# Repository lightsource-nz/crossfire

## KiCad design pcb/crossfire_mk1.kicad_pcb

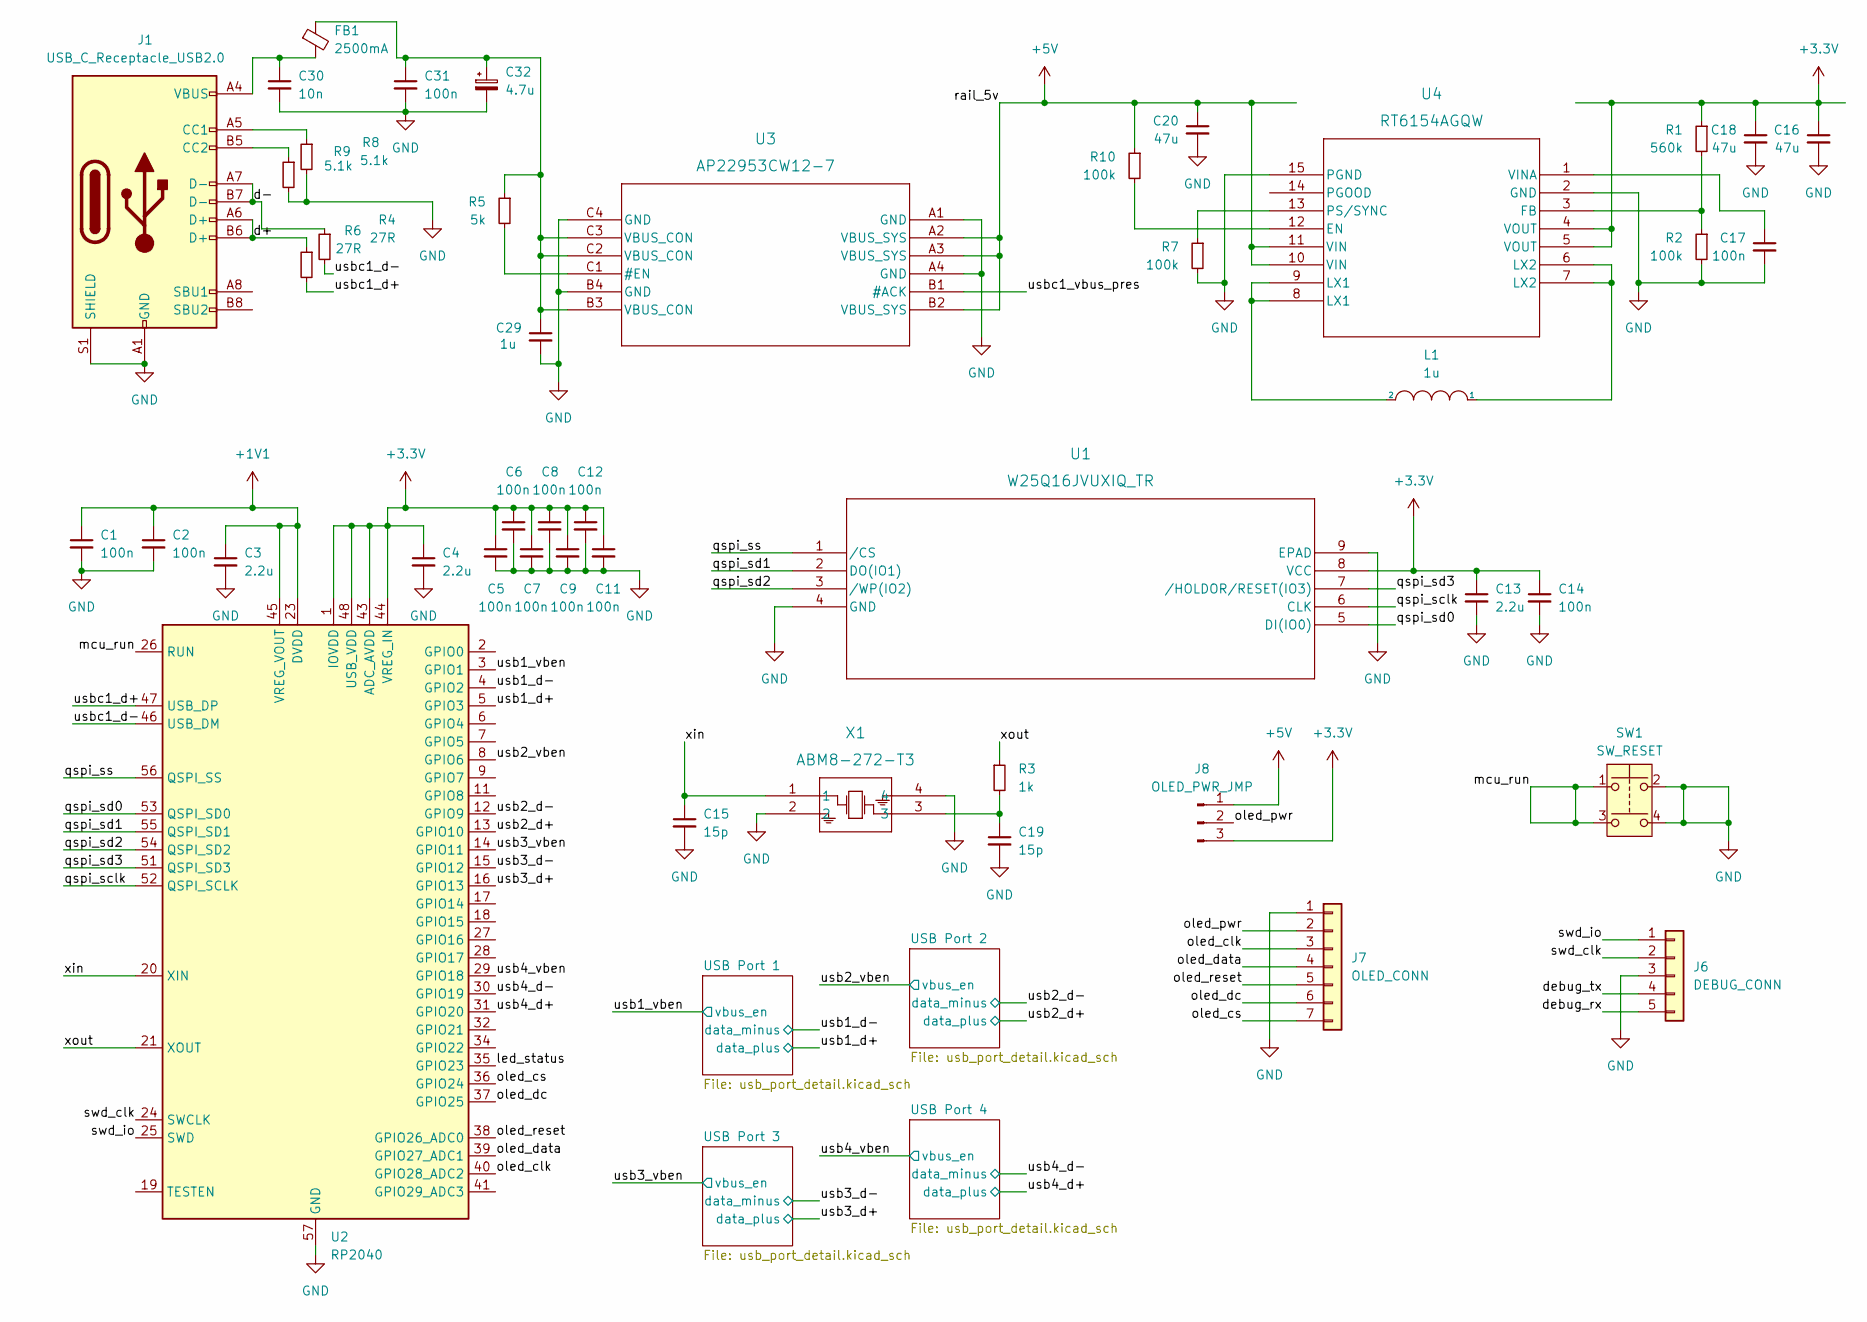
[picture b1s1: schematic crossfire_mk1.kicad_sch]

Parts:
C1, C2, C5, C6, C7, C8, C9, C11, C12, C14, C17, C31: 100n; C_0201_0603Metric
C3, C4: 2.2u; C_0402_1005Metric_Pad0.74x0.62mm_HandSolder
C13: 2.2u; C_0402_1005Metric
C15, C19: 15p; C_0201_0603Metric
C16, C18, C20: 47u; C_0805_2012Metric
C29: 1u; C_0201_0603Metric
C30: 10n; C_0201_0603Metric
C32: 4.7u; CP_Elec_4x5.4
FB1: 2500mA; L_0603_1608Metric
J1: USB_C_Receptacle_USB2.0; USB_C_Receptacle_GCT_USB4085
J6: DEBUG_CONN; PinHeader_1x05_P2.54mm_Vertical
J7: OLED_CONN; PinHeader_1x07_P2.54mm_Vertical
J8: OLED_PWR_JMP; PinHeader_1x03_P2.54mm_Vertical
L1: 1u; L_0805_2012Metric_Pad1.05x1.20mm_HandSolder
R1: 560k; R_0201_0603Metric
R2, R7, R10: 100k; R_0201_0603Metric
R3: 1k; R_0201_0603Metric
R4, R6: 27R; R_0201_0603Metric
R5: 5k; R_0201_0603Metric
R8, R9: 5.1k; R_0201_0603Metric
SW1: SW_RESET; Sumida_CPFC6D36NP-100M06
U1: W25Q16JVUXIQ_TR; W25Q16JVUXIQ_TR_PSON50P300X200X60-9N
U2: RP2040; QFN-56-1EP_7x7mm_P0.4mm_EP3.2x3.2mm
U3: AP22953CW12-7; BGA12_AP22953CW12-7_DIO
U4: RT6154AGQW; QFN_4AGQW_RIT
X1: ABM8-272-T3; ABM8-272-T3_ABR

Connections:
+1V1: C1.1, C2.1, C3.1, U2.23 (DVDD), U2.45 (VREG_VOUT), U2.50 (DVDD)
+3.3V: C4.1, C5.1, C6.1, C7.1, C8.1, C9.1, C11.1, C12.1, C13.1, C14.1, C16.1, C18.1, J8.3, R1.1, U1.8 (VCC), U2.1 (IOVDD), U2.10 (IOVDD), U2.22 (IOVDD), U2.33 (IOVDD), U2.42 (IOVDD), U2.43 (ADC_AVDD), U2.44 (VREG_IN), U2.48 (USB_VDD), U2.49 (IOVDD), U4.4 (VOUT), U4.5 (VOUT)
+5V: C20.1, J8.1, R10.1, U3.A2 (VBUS_SYS), U3.A3 (VBUS_SYS), U3.B2 (VBUS_SYS), U4.10 (VIN), U4.11 (VIN); also elsewhere on the board
/d+: J1.A6 (D+), J1.B6 (D+), R6.1
/d-: J1.A7 (D-), J1.B7 (D-), R4.1
/debug_rx: J6.5
/debug_tx: J6.4
/led_status: U2.35 (GPIO23)
/mcu_run: SW1.1, SW1.3, U2.26 (RUN)
/oled_clk: J7.3, U2.40 (GPIO28_ADC2)
/oled_cs: J7.7, U2.36 (GPIO24)
/oled_data: J7.4, U2.39 (GPIO27_ADC1)
/oled_dc: J7.6, U2.37 (GPIO25)
/oled_pwr: J7.2, J8.2
/oled_reset: J7.5, U2.38 (GPIO26_ADC0)
/qspi_sclk: U1.6 (CLK), U2.52 (QSPI_SCLK)
/qspi_sd0: U1.5 (DI(IO0)), U2.53 (QSPI_SD0)
/qspi_sd1: U1.2 (DO(IO1)), U2.55 (QSPI_SD1)
/qspi_sd2: U1.3 (/WP(IO2)), U2.54 (QSPI_SD2)
/qspi_sd3: U1.7 (/HOLDOR/RESET(IO3)), U2.51 (QSPI_SD3)
/qspi_ss: U1.1 (/CS), U2.56 (QSPI_SS)
/swd_clk: J6.2, U2.24 (SWCLK)
/swd_io: J6.1, U2.25 (SWD)
/usb1_d+: U2.5 (GPIO3); also elsewhere on the board
/usb1_d-: U2.4 (GPIO2); also elsewhere on the board
/usb1_vben: U2.3 (GPIO1); also elsewhere on the board
/usb2_d+: U2.13 (GPIO10); also elsewhere on the board
/usb2_d-: U2.12 (GPIO9); also elsewhere on the board
/usb2_vben: U2.8 (GPIO6); also elsewhere on the board
/usb3_d+: U2.16 (GPIO13); also elsewhere on the board
/usb3_d-: U2.15 (GPIO12); also elsewhere on the board
/usb3_vben: U2.14 (GPIO11); also elsewhere on the board
/usb4_d+: U2.31 (GPIO20); also elsewhere on the board
/usb4_d-: U2.30 (GPIO19); also elsewhere on the board
/usb4_vben: U2.29 (GPIO18); also elsewhere on the board
/usbc1_d+: R6.2, U2.47 (USB_DP)
/usbc1_d-: R4.2, U2.46 (USB_DM)
/usbc1_vbus_pres: U3.B1 (#ACK)
/xin: C15.1, U2.20 (XIN), X1.1
/xout: R3.1, U2.21 (XOUT)
GND: C1.2, C2.2, C3.2, C4.2, C5.2, C6.2, C7.2, C8.2, C9.2, C11.2, C12.2, C13.2, C14.2, C15.2, C16.2, C17.2, C18.2, C19.2, C20.2, C29.2, C30.2, C31.2, C32.2, J1.A1 (GND), J1.A12 (GND), J1.B1 (GND), J1.B12 (GND), J1.S1 (SHIELD), J6.3, J7.1, R2.2, R7.2, R8.2, R9.2, SW1.2, SW1.4, U1.4 (GND), U1.9 (EPAD), U2.57 (GND), U3.A1 (GND), U3.A4 (GND), U3.B4 (GND), U3.C4 (GND), U4.2 (GND), U4.15 (PGND), X1.2, X1.4; also elsewhere on the board
unnamed: C19.1, R3.2, X1.3
unnamed: C29.1, C31.1, C32.1, FB1.1, R5.1, U3.B3 (VBUS_CON), U3.C2 (VBUS_CON), U3.C3 (VBUS_CON)
unnamed: C30.1, FB1.2, J1.A4 (VBUS), J1.A9 (VBUS), J1.B4 (VBUS), J1.B9 (VBUS)
unnamed: J1.A5 (CC1), R8.1
unnamed: J1.B5 (CC2), R9.1
unnamed: L1.1, U4.6 (LX2), U4.7 (LX2)
unnamed: L1.2, U4.8 (LX1), U4.9 (LX1)
unnamed: R5.2, U3.C1 (#EN)
unnamed: R10.2, U4.12 (EN)
unnamed: R1.2, R2.1, U4.3 (FB)
unnamed: R7.1, U4.13 (PS/SYNC)
unnamed: C17.1, U4.1 (VINA)

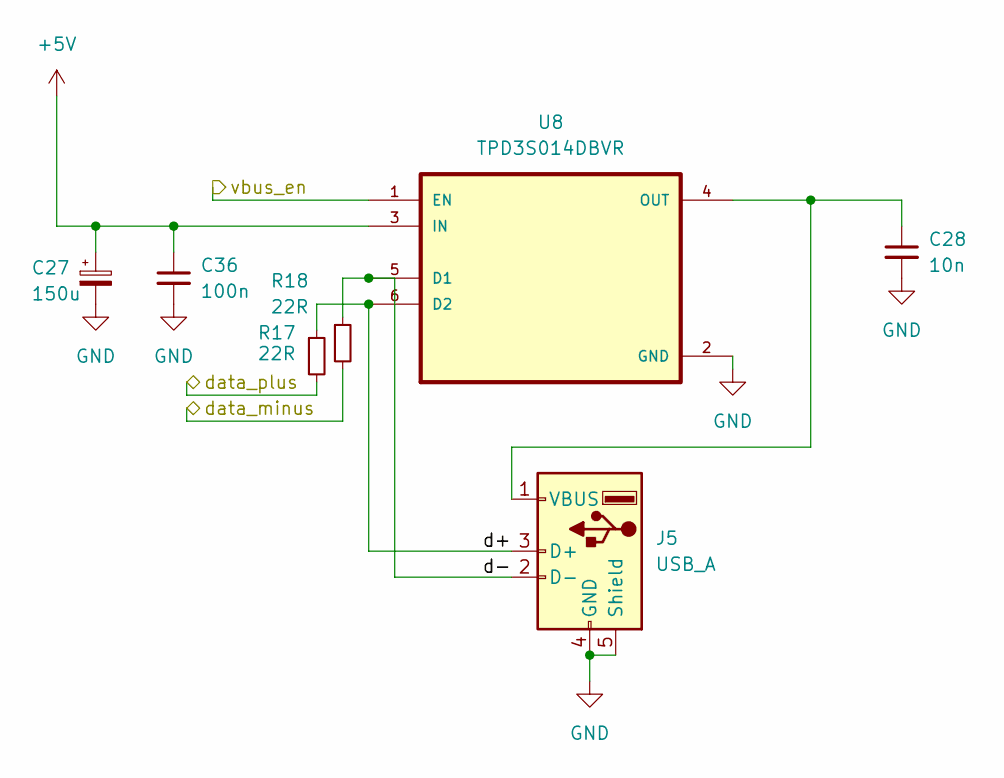
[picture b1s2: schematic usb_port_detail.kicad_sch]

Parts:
C27: 150u; CP_Elec_6.3x7.7
C28: 10n; C_0201_0603Metric
C36: 100n; C_0201_0603Metric
J5: USB_A; USB_A_Molex_67643_Horizontal
R17, R18: 22R; R_0201_0603Metric_Pad0.64x0.40mm_HandSolder
U8: TPD3S014DBVR; TPD3S014DBVR_SOT95P280X145-6N

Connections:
+5V: C27.1, C36.1, U8.3 (IN); also elsewhere on the board
/USB Port 4/d+: J5.3 (D+), R17.1, U8.6 (D2)
/USB Port 4/d-: J5.2 (D-), R18.1, U8.5 (D1)
/usb4_d+: R17.2; also elsewhere on the board
/usb4_d-: R18.2; also elsewhere on the board
/usb4_vben: U8.1 (EN); also elsewhere on the board
GND: C27.2, C28.2, C36.2, J5.4 (GND), J5.5 (Shield), U8.2 (GND); also elsewhere on the board
unnamed: C28.1, J5.1 (VBUS), U8.4 (OUT)

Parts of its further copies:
C21, C23, C25: 150u; CP_Elec_6.3x7.7
C22, C24, C26: 10n; C_0201_0603Metric
C33, C34, C35: 100n; C_0201_0603Metric
J2, J3, J4: USB_A; USB_A_Molex_67643_Horizontal
R11, R12, R13, R14, R15, R16: 22R; R_0201_0603Metric_Pad0.64x0.40mm_HandSolder
U5, U6, U7: TPD3S014DBVR; TPD3S014DBVR_SOT95P280X145-6N

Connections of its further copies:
+5V: C21.1, C23.1, C25.1, C33.1, C34.1, C35.1, U5.3 (IN), U6.3 (IN), U7.3 (IN); also elsewhere on the board
/USB Port 1/d+: J2.3 (D+), R11.1, U5.6 (D2)
/USB Port 1/d-: J2.2 (D-), R12.1, U5.5 (D1)
/USB Port 2/d+: J3.3 (D+), R13.1, U6.6 (D2)
/USB Port 2/d-: J3.2 (D-), R14.1, U6.5 (D1)
/USB Port 3/d+: J4.3 (D+), R15.1, U7.6 (D2)
/USB Port 3/d-: J4.2 (D-), R16.1, U7.5 (D1)
/usb1_d+: R11.2; also elsewhere on the board
/usb1_d-: R12.2; also elsewhere on the board
/usb1_vben: U5.1 (EN); also elsewhere on the board
/usb2_d+: R13.2; also elsewhere on the board
/usb2_d-: R14.2; also elsewhere on the board
/usb2_vben: U6.1 (EN); also elsewhere on the board
/usb3_d+: R15.2; also elsewhere on the board
/usb3_d-: R16.2; also elsewhere on the board
/usb3_vben: U7.1 (EN); also elsewhere on the board
GND: C21.2, C22.2, C23.2, C24.2, C25.2, C26.2, C33.2, C34.2, C35.2, J2.4 (GND), J2.5 (Shield), J3.4 (GND), J3.5 (Shield), J4.4 (GND), J4.5 (Shield), U5.2 (GND), U6.2 (GND), U7.2 (GND); also elsewhere on the board
unnamed: C22.1, J2.1 (VBUS), U5.4 (OUT)
unnamed: C24.1, J3.1 (VBUS), U6.4 (OUT)
unnamed: C26.1, J4.1 (VBUS), U7.4 (OUT)

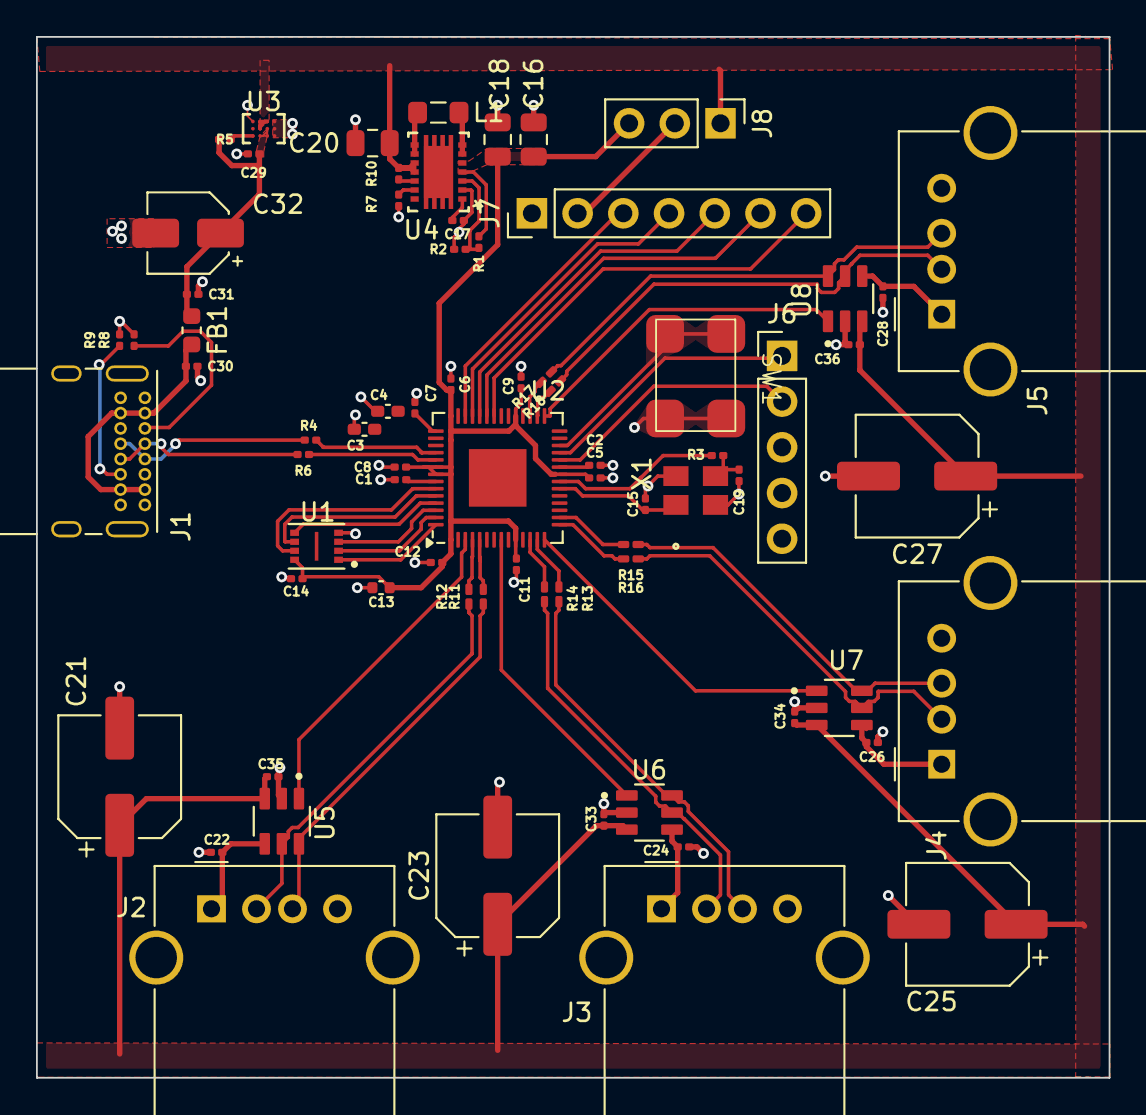
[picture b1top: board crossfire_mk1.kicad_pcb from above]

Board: 2 copper layers, 59.6 x 57.8 mm, 73 parts (0 on the bottom side), 61 nets.

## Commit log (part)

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2023-05-29 initial import
2024-08-03 add pcb design files
2024-08-07 integrate debug and oled connectors
